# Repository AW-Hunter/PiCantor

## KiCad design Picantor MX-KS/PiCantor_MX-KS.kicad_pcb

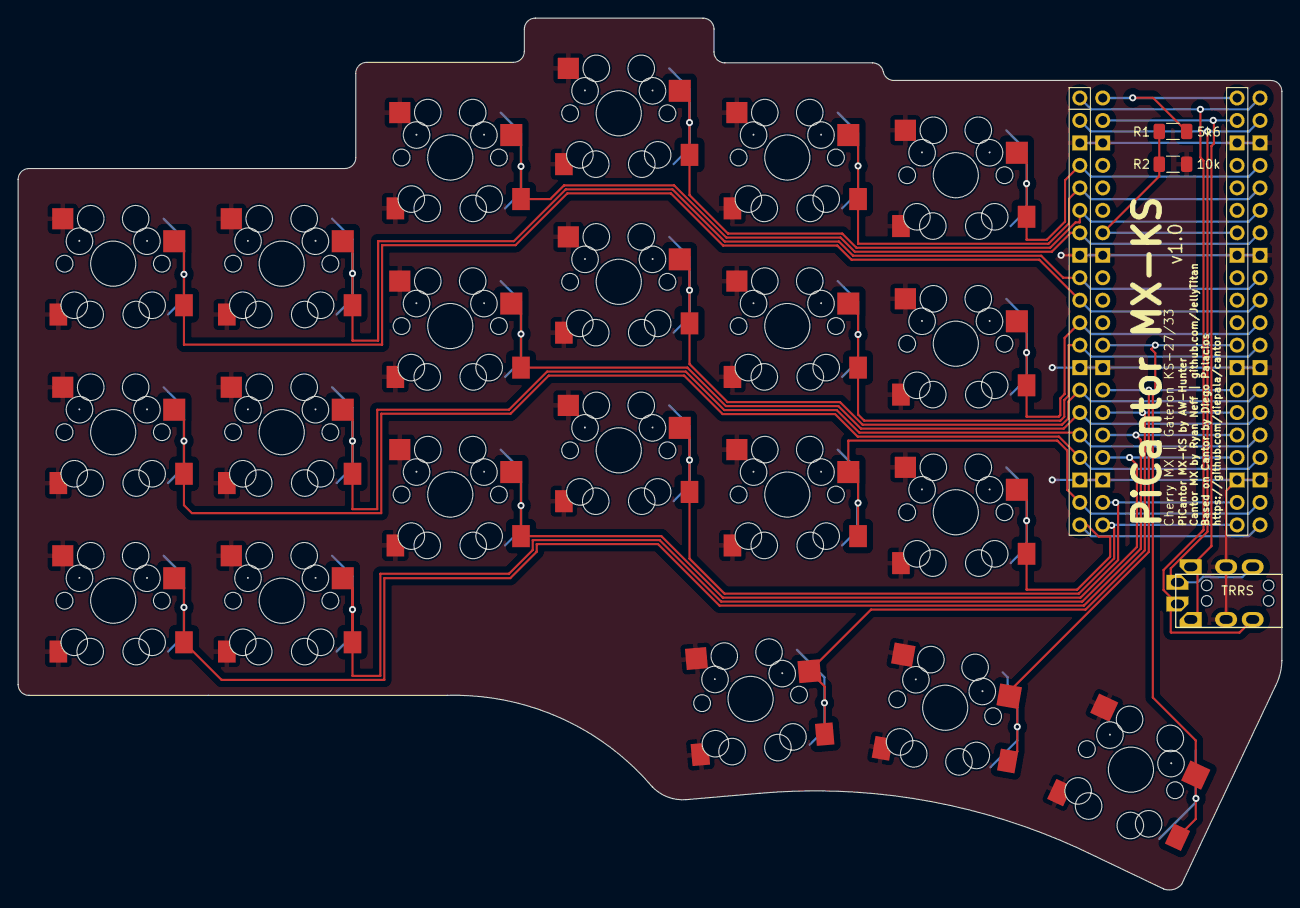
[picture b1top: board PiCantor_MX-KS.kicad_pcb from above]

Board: 2 copper layers, 142.9 x 98.6 mm, 25 parts (0 on the bottom side), 27 nets.

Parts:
J1: TRRS; MJ-4PP-9_Cantor_MX_TX-RX_Crossover
K00, K01, K02, K03, K04, K05, K10, K11, K12, K13, K14, K15, K20, K21, K22, K23, K24, K25, K30, K31, K32: KEYSW; CherryMX_Gateron KS
R1: 5k6; R_1206_3216Metric_Pad1.30x1.75mm_HandSolder
R2: 10k; R_1206_3216Metric_Pad1.30x1.75mm_HandSolder
U1: YAAJ_WeAct_BlackPill_Part_Like; Cantor_DS_YAAJ_WeAct_BlackPill_2

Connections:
/RX: J1.1 (SLEEVE), J1.4 (RING2), U1.2 (PB13)
/TX: J1.1 (SLEEVE), J1.3 (RING1), U1.1 (PB12)
/k00: K00.1, U1.10 (PA15)
/k01: K01.1, U1.9 (PA12)
/k02: K02.1, U1.7 (PA10)
/k03: K03.1, U1.6 (PA9)
/k04: K04.1, U1.5 (PA8)
/k05: K05.1, U1.4 (PB15)
/k10: K10.1, U1.17 (PB9)
/k11: K11.1, U1.16 (PB8)
/k12: K12.1, U1.15 (PB7)
/k13: K13.1, U1.14 (PB6)
/k14: K14.1, U1.12 (PB4)
/k15: K15.1, U1.11 (PB3)
/k20: K20.1, U1.25 (RES)
/k21: K21.1, U1.24 (PC15)
/k22: K22.1, U1.22 (PC13)
/k23: K23.1, U1.21 (VBat)
/k24: K24.1, U1.19 (GND)
/k25: K25.1, U1.20 (3V3)
/k30: K30.1, U1.26 (PA0)
/k31: K31.1, U1.27 (PA1)
/k32: K32.1, U1.29 (PA3)
GND: J1.3 (RING1), J1.4 (RING2), K00.2, K01.2, K02.2, K03.2, K04.2, K05.2, K10.2, K11.2, K12.2, K13.2, K14.2, K15.2, K20.2, K21.2, K22.2, K23.2, K24.2, K25.2, K30.2, K31.2, K32.2, R2.2, U1.3 (PB14), U1.8 (PA11), U1.13 (PB5), U1.18 (5V), U1.23 (PC14), U1.28 (PA2), U1.33 (PA7), U1.38 (3V3)
VBUS: R1.1, U1.40 (5V)
VBUS_SENSE: R1.2, R2.1, U1.34 (PB0)
VCC: J1.2 (TIP), U1.39 (GND)

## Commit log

2024-03-11 Create Create
